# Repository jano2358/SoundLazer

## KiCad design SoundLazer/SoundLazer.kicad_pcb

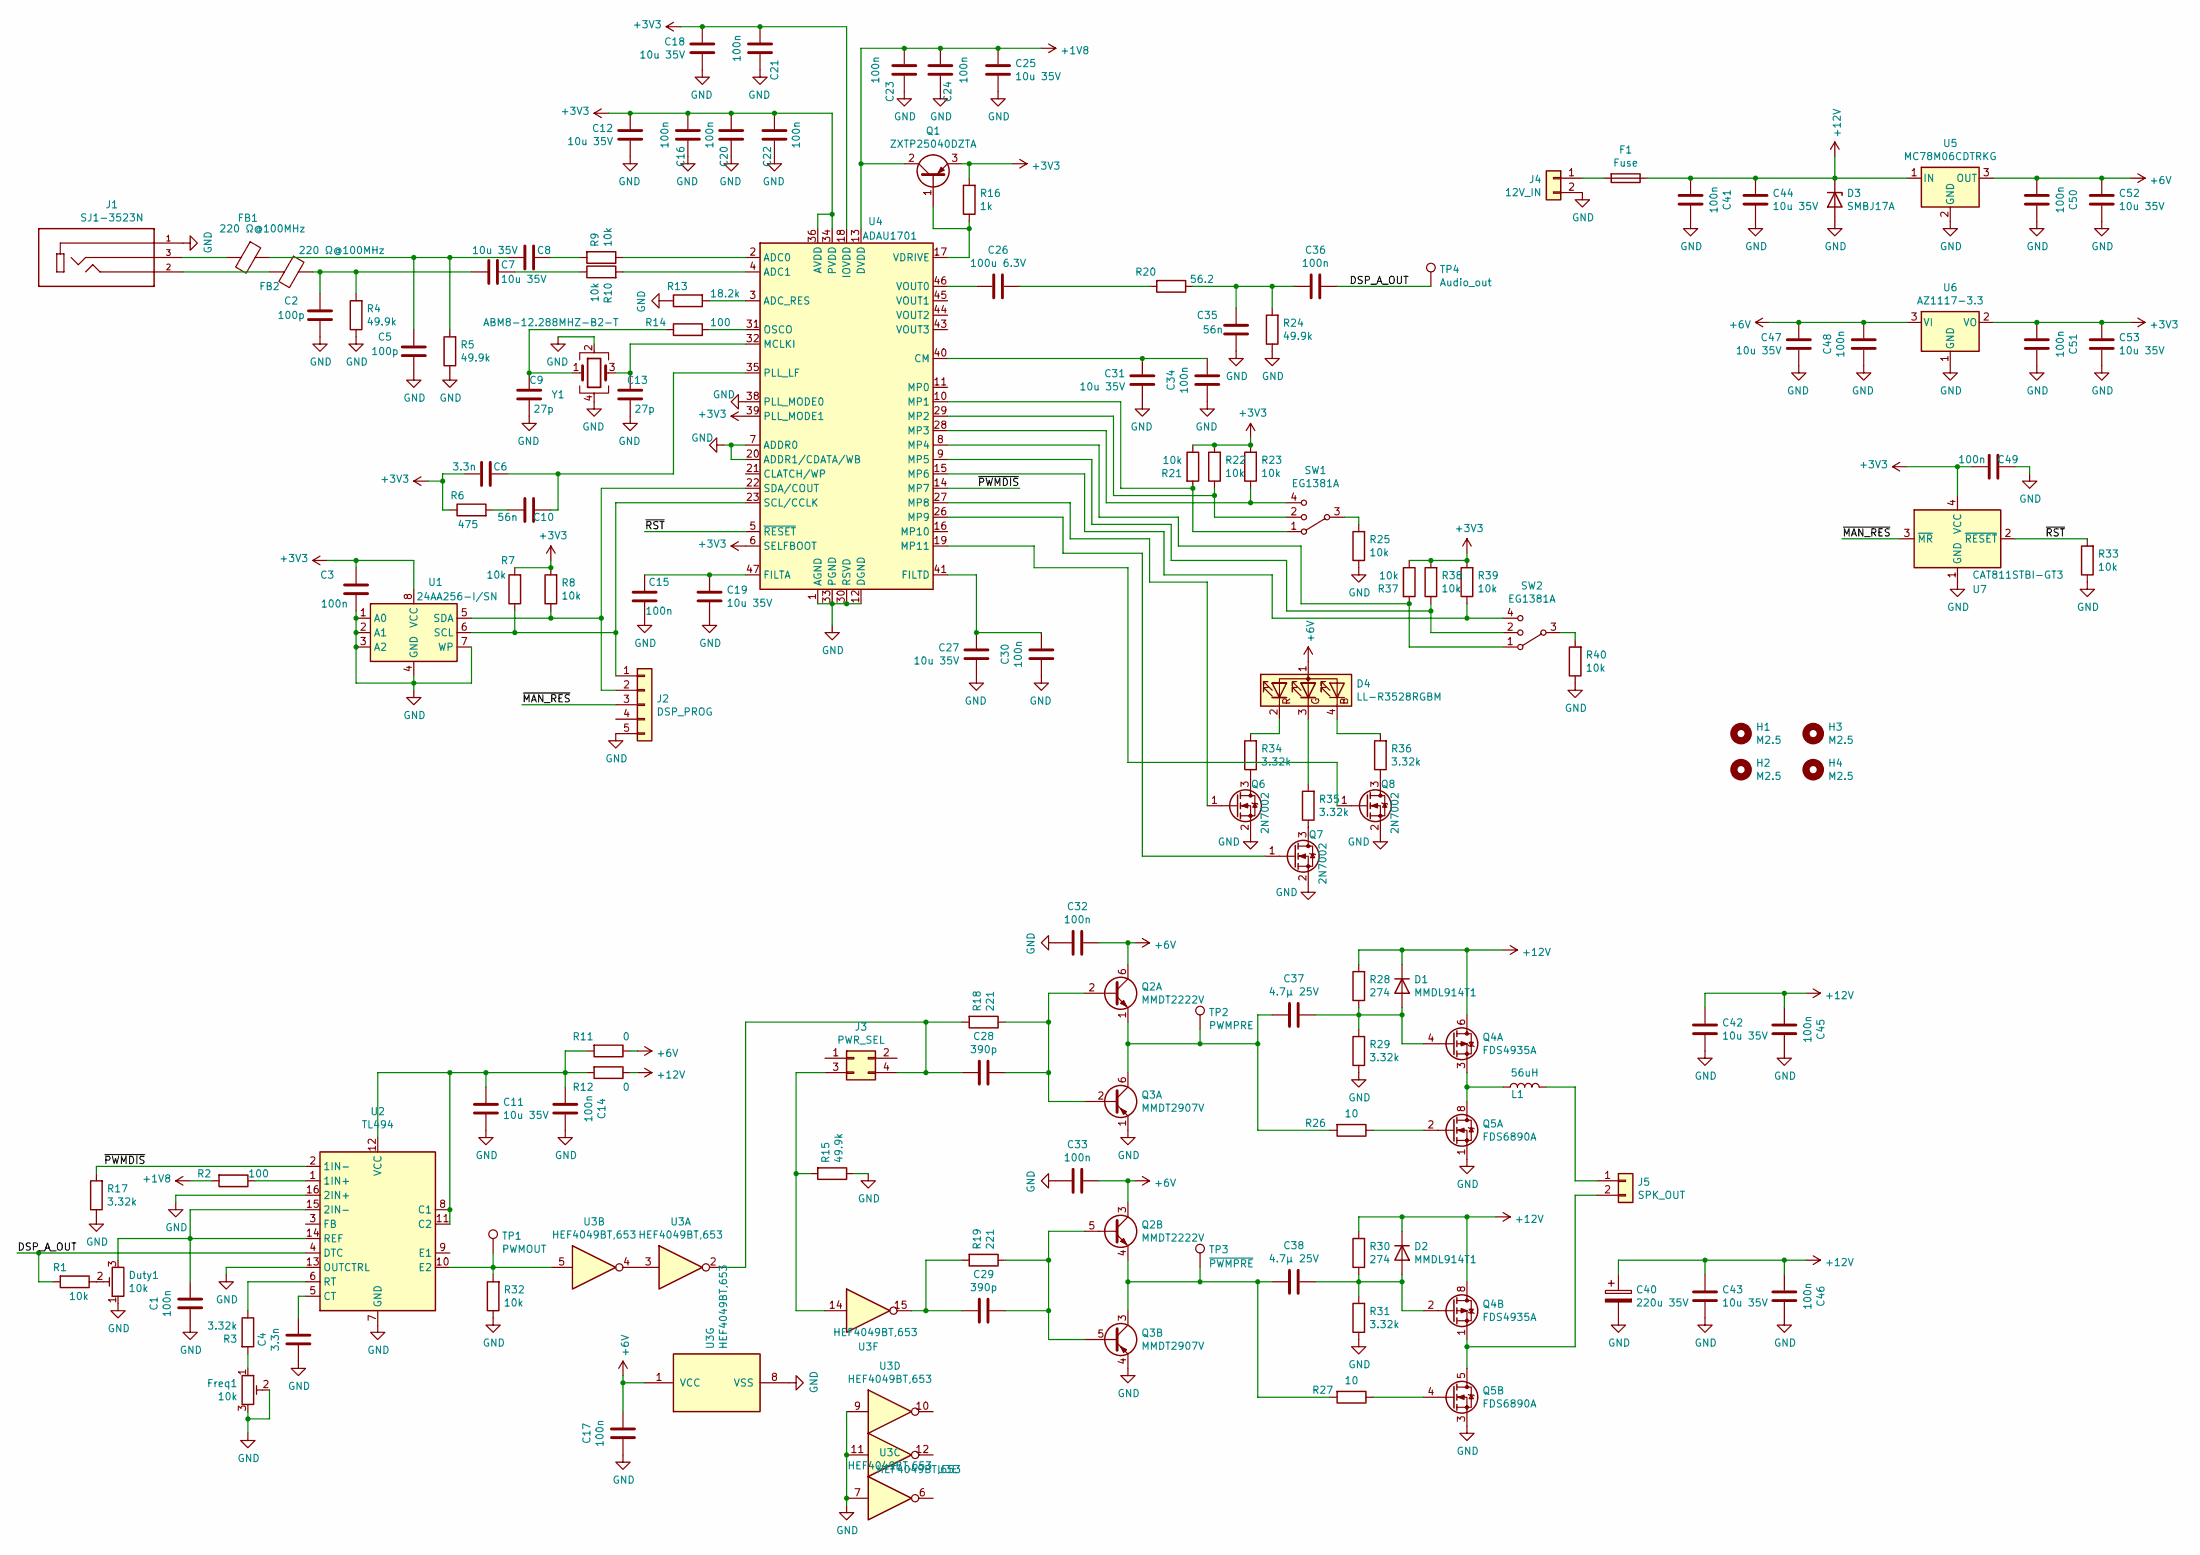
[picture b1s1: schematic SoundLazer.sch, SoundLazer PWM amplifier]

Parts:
C1, C3, C14, C15, C16, C17, C20, C21, C22, C23, C24, C32, C33, C34, C36, C41, C45, C46, C48, C49, C50, C51: 100n; C_0402_1005Metric
C2: 100p; C_0402_1005Metric
C4, C6: 3.3n; C_0603_1608Metric
C5: 100p; C_0603_1608Metric
C7, C8, C11, C12, C18, C19, C25, C27, C31, C42, C43, C44, C47, C52, C53: 10u 35V; C_0805_2012Metric
C9, C13: 27p; C_0603_1608Metric
C10, C35: 56n; C_0603_1608Metric
C26: 100u 6.3V; C_1206_3216Metric
C28, C29: 390p; C_0603_1608Metric
C30: 100n; C_0603_1608Metric
C37, C38: 4.7µ 25V; C_0603_1608Metric
C40: 220u 35V; C_Elec_8x10.2
D1, D2: MMDL914T1; D_SOD-323
D3: SMBJ17A; D_SMB
D4: LL-R3528RGBM; LED_Avago_PLCC4_3.2x2.8mm_CW
Duty1: 10k; Potentiometer_Bourns_3266Y_Vertical
F1: Fuse; Fuse_1206_3216Metric
FB1, FB2: 220 Ω@100MHz; L_0603_1608Metric
Freq1: 10k; Potentiometer_Bourns_3266Y_Vertical
H1, H2, H3, H4: M2.5; MountingHole_2.7mm_M2.5
J1: SJ1-3523N; CUI_SJ1-3523N; PARTREV 1.02
J2: DSP_PROG; PinHeader_1x05_P2.54mm_Vertical
J3: PWR_SEL; PinHeader_2x02_P2.54mm_Vertical
J4: 12V_IN; PhoenixContact_MCV_1,5_2-G-3.5_1x02_P3.50mm_Vertical; PartNumber 1713017
J5: SPK_OUT; PhoenixContact_MCV_1,5_2-G-3.5_1x02_P3.50mm_Vertical; PartNumber 1713017
L1: 56uH; L_10.4x10.4_H4.8
Q1: ZXTP25040DZTA; SOT-89-3
Q2: MMDT2222V; SOT-563
Q3: MMDT2907V; SOT-563
Q4: FDS4935A; SOIC-8_3.9x4.9mm_P1.27mm
Q5: FDS6890A; SOIC-8_3.9x4.9mm_P1.27mm
Q6, Q7, Q8: 2N7002; SOT-23
R1, R7, R8, R9, R10, R21, R22, R23, R25, R32, R33, R37, R38, R39, R40: 10k; R_0402_1005Metric
R2, R14: 100; R_0402_1005Metric
R3, R17, R29, R31, R34, R35, R36: 3.32k; R_0402_1005Metric
R4, R5, R15, R24: 49.9k; R_0402_1005Metric
R6: 475; R_0402_1005Metric
R11, R12: 0; R_0402_1005Metric
R13: 18.2k; R_0402_1005Metric
R16: 1k; R_0402_1005Metric
R18, R19: 221; R_0402_1005Metric
R20: 56.2; R_0402_1005Metric
R26, R27: 10; R_0402_1005Metric
R28, R30: 274; R_0402_1005Metric
SW1, SW2: EG1381A; SW_SP3T_PCM13
TP1: PWMOUT; TestPoint_THTPad_D1.5mm_Drill0.7mm
TP2: PWMPRE; TestPoint_THTPad_D1.5mm_Drill0.7mm
TP3: ~PWMPRE; TestPoint_THTPad_D1.5mm_Drill0.7mm
TP4: Audio_out; TestPoint_THTPad_D1.5mm_Drill0.7mm
U1: 24AA256-I/SN; SOIC-8_3.9x4.9mm_P1.27mm
U2: TL494; TSSOP-16_4.4x5mm_P0.65mm
U3: HEF4049BT,653; SOIC-16_3.9x9.9mm_P1.27mm
U4: ADAU1701; LQFP-48_7x7mm_P0.5mm
U5: MC78M06CDTRKG; TO-252-2
U6: AZ1117-3.3; SOT-223
U7: CAT811STBI-GT3; SOT-143
Y1: ABM8-12.288MHZ-B2-T; Crystal_SMD_Abracon_ABM8G-4Pin_3.2x2.5mm

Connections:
+1V8: C23.1, C24.2, C25.1, Q1.2 (C), R2.2, U4.13 (DVDD), U4.24 (DVDD)
+3V3: C3.2, C6.2, C12.1, C16.2, C18.1, C20.2, C21.2, C22.2, C49.1, C51.2, C53.1, Q1.3 (E), R6.1, R7.2, R8.2, R16.2, R21.1, R22.2, R23.2, R37.1, R38.2, R39.2, U1.8 (VCC), U4.6 (SELFBOOT), U4.18 (IOVDD), U4.34 (PVDD), U4.36 (AVDD), U4.39 (PLL_MODE1), U4.48 (AVDD), U6.2 (VO), U7.4 (VCC)
+6V: C17.1, C32.1, C33.1, C47.1, C48.2, C50.2, C52.1, D4.1 (A), Q2.3 (C2), Q2.6 (C1), R11.1, U3.1 (VCC), U5.3 (OUT), U6.3 (VI)
+12V: C40.1, C41.2, C42.1, C43.1, C44.1, C45.2, C46.2, D1.1 (K), D2.1 (K), D3.1 (K), F1.1, Q4.5 (D), Q4.6 (D), Q4.7 (D), Q4.8 (D), R12.1, R28.2, R30.2, U5.1 (IN)
/DSP_A_OUT: C36.1, R1.2, TP4.1, U2.4 (DTC)
/~MAN_RES: J2.3, U7.3 (~MR)
/~PWMDIS: R17.2, U2.2 (1IN-), U4.14 (MP7)
/~RST: R33.2, U4.5 (~RESET), U7.2 (~RESET)
GND: C1.2, C2.2, C3.1, C4.2, C5.2, C9.1, C11.2, C12.2, C13.1, C14.1, C15.1, C16.1, C17.2, C18.2, C19.2, C20.1, C21.1, C22.1, C23.2, C24.1, C25.2, C27.2, C30.1, C31.2, C32.2, C33.2, C34.1, C35.2, C40.2, C41.1, C42.2, C43.2, C44.2, C45.1, C46.1, C47.2, C48.1, C49.2, C50.1, C51.1, C52.2, C53.2, D3.2 (A), Duty1.1, Freq1.2, Freq1.3, J1.1, J2.5, J4.2, Q3.1 (E), Q3.4 (E), Q5.1 (S1), Q5.3 (S2), Q6.2 (S), Q7.2 (S), Q8.2 (S), R4.1, R5.1, R13.1, R15.1, R17.1, R24.1, R25.1, R29.1, R31.1, R32.1, R33.1, R40.1, U1.1 (A0), U1.2 (A1), U1.3 (A2), U1.4 (GND), U1.7 (WP), U2.7 (GND), U2.13 (OUTCTRL), U2.16 (2IN+), U3.7, U3.8 (VSS), U3.9, U3.11, U4.1 (AGND), U4.7 (ADDR0), U4.12 (DGND), U4.20 (ADDR1/CDATA/WB), U4.25 (DGND), U4.30 (RSVD), U4.33 (PGND), U4.37 (AGND), U4.38 (PLL_MODE0), U4.42 (AGND), U5.2 (GND), U6.1 (GND), U7.1 (GND), Y1.2, Y1.4
unnamed: C1.1, Duty1.3, U2.14 (REF), U2.15 (2IN-)
unnamed: C2.1, C7.2, FB2.1, R4.2
unnamed: C4.1, U2.5 (CT)
unnamed: C5.1, C8.2, FB1.1, R5.2
unnamed: C7.1, R10.1
unnamed: C8.1, R9.2
unnamed: C9.2, R14.1, Y1.1
unnamed: C6.1, C10.1, U4.35 (PLL_LF)
unnamed: C10.2, R6.2
unnamed: C11.1, C14.2, R11.2, R12.2, U2.8 (C1), U2.11 (C2), U2.12 (VCC)
unnamed: C13.2, U4.32 (MCLKI), Y1.3
unnamed: C15.2, C19.1, U4.47 (FILTA)
unnamed: C26.1, R20.2
unnamed: C26.2, U4.46 (VOUT0)
unnamed: C27.1, C30.2, U4.41 (FILTD)
unnamed: C28.1, Q2.2 (B1), Q3.2 (B), R18.1
unnamed: C28.2, J3.4, R18.2, U3.2
unnamed: C29.1, Q2.5 (B2), Q3.5 (B), R19.1
unnamed: C29.2, R19.2, U3.15
unnamed: C31.1, C34.2, U4.40 (CM)
unnamed: C35.1, C36.2, R20.1, R24.2
unnamed: C37.1, D1.2 (A), Q4.4 (G), R28.1, R29.2
unnamed: C37.2, Q2.1 (E1), Q3.6 (C), R26.2, TP2.1
unnamed: C38.1, D2.2 (A), Q4.2 (G), R30.1, R31.2
unnamed: C38.2, Q2.4 (E2), Q3.3 (C), R27.2, TP3.1
unnamed: D4.2 (RK), R34.2
unnamed: D4.3 (GK), R35.2
unnamed: D4.4 (BK), R36.2
unnamed: Duty1.2, R1.1
unnamed: F1.2, J4.1
unnamed: FB1.2, J1.3
unnamed: FB2.2, J1.2
unnamed: Freq1.1, R3.2
unnamed: J2.1, R7.1, U1.6 (SCL), U4.23 (SCL/CCLK)
unnamed: J2.2, R8.1, U1.5 (SDA), U4.22 (SDA/COUT)
unnamed: J3.3, R15.2, U3.14
unnamed: J5.1, L1.2
unnamed: J5.2, Q4.1 (S), Q5.5 (D2), Q5.6 (D2)
unnamed: L1.1, Q4.3 (S), Q5.7 (D1), Q5.8 (D1)
unnamed: Q1.1 (B), R16.1, U4.17 (VDRIVE)
unnamed: Q5.2 (G1), R26.1
unnamed: Q5.4 (G2), R27.1
unnamed: Q6.1 (G), U4.27 (MP8)
unnamed: Q6.3 (D), R34.1
unnamed: Q7.1 (G), U4.26 (MP9)
unnamed: Q7.3 (D), R35.1
unnamed: Q8.1 (G), U4.19 (MP11)
unnamed: Q8.3 (D), R36.1
unnamed: R2.1, U2.1 (1IN+)
unnamed: R3.1, U2.6 (RT)
unnamed: R9.1, U4.2 (ADC0)
unnamed: R10.2, U4.4 (ADC1)
unnamed: R13.2, U4.3 (ADC_RES)
unnamed: R14.2, U4.31 (OSCO)
unnamed: R21.2, SW1.1, U4.10 (MP1)
unnamed: R22.1, SW1.2, U4.29 (MP2)
unnamed: R23.1, SW1.4, U4.28 (MP3)
unnamed: R25.2, SW1.3
unnamed: R32.2, TP1.1, U2.10 (E2), U3.5
unnamed: R37.2, SW2.1, U4.8 (MP4)
unnamed: R38.1, SW2.2, U4.9 (MP5)
unnamed: R39.1, SW2.4, U4.15 (MP6)
unnamed: R40.2, SW2.3
unnamed: U3.3, U3.4

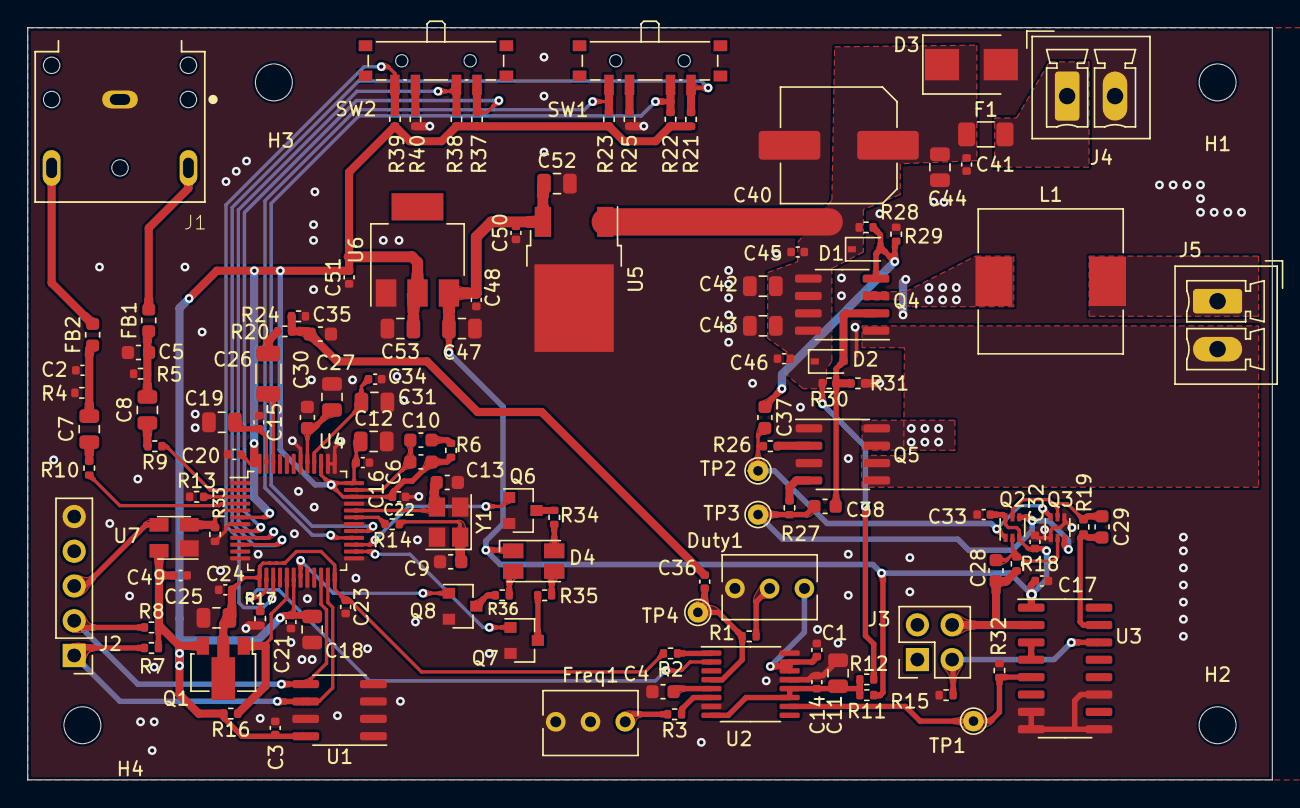
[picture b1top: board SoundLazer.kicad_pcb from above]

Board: 2 copper layers, 91.0 x 55.0 mm, 133 parts (0 on the bottom side), 73 nets.

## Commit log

2021-06-04 cache add
2021-06-05 first revision
2021-06-05 r20 corr
2021-06-14 pcb update
2021-06-18 pcb_finish
2021-07-04 gerbers ready
